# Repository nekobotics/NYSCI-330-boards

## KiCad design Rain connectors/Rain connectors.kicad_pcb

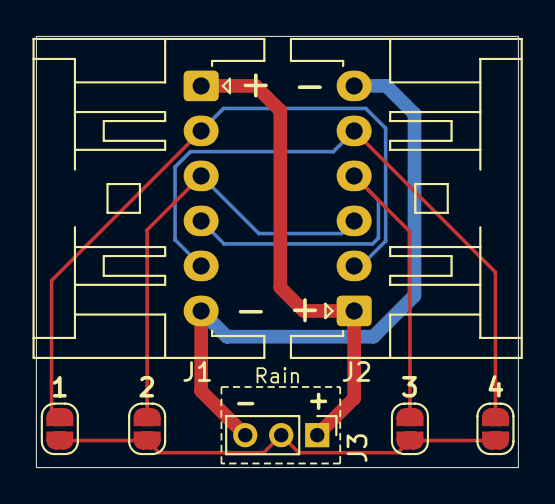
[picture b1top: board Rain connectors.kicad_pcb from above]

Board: 2 copper layers, 26.8 x 24.0 mm, 7 parts (0 on the bottom side), 7 nets.

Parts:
1, 2, 3, 4: Jumper_2_Open; SolderJumper-2_P1.3mm_Open_RoundedPad1.0x1.5mm
J1, J2: Conn_01x06_Socket; JST_XA_S06B-XASK-1_1x06_P2.50mm_Horizontal
J3: Conn_01x03_Socket; PinHeader_1x03_P2.00mm_Vertical

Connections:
+5V: J1.1, J2.1, J3.1
GND: J1.6, J2.6, J3.3
unnamed: 1.2 (B), J1.2, J2.2
unnamed: 2.2 (B), J1.3, J2.3
unnamed: 3.2 (B), J1.4, J2.4
unnamed: 4.2 (B), J1.5, J2.5
unnamed: 1.1 (A), 2.1 (A), 3.1 (A), 4.1 (A), J3.2

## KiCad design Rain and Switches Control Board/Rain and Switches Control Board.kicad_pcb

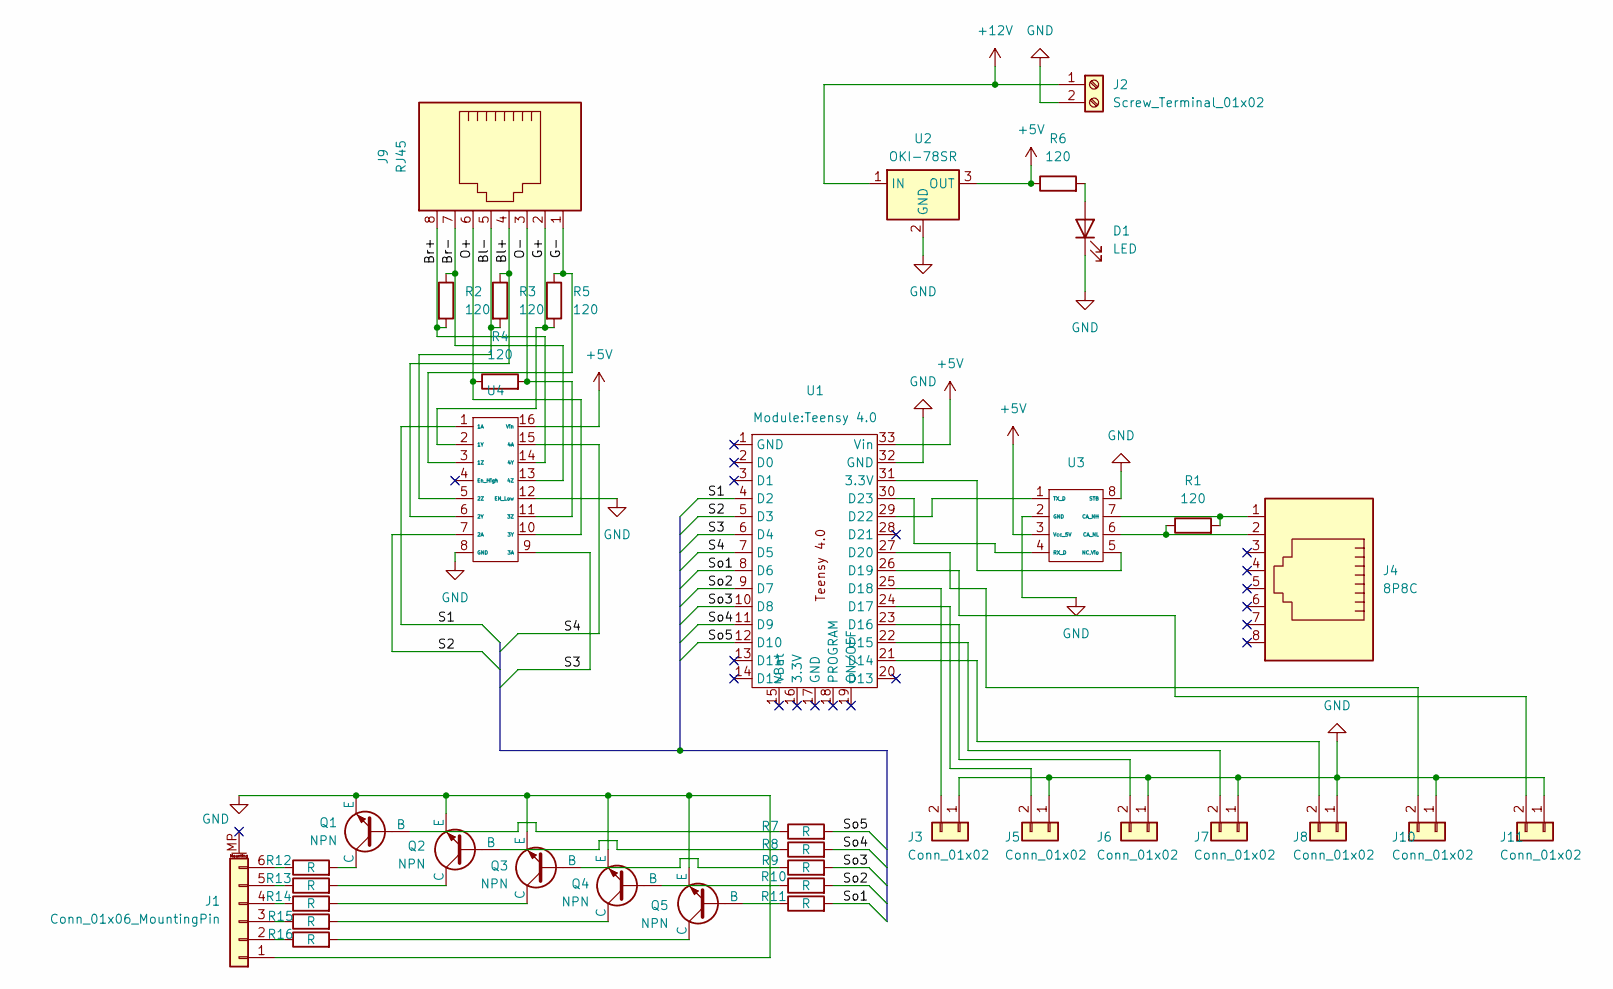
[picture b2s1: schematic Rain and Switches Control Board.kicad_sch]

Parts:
D1: LED; LED_D3.0mm
J1: Conn_01x06_MountingPin; PhoenixContact_MC_1,5_6-G-3.5_1x06_P3.50mm_Horizontal
J2: Screw_Terminal_01x02; TerminalBlock_Wago_2x1_2604_1102
J3, J5, J6, J7, J8, J10, J11: Conn_01x02; TerminalBlock_Altech_AK300-2_P5.00mm
J4: 8P8C; RJ45_Ninigi_GE
J9: RJ45; RJ45_Ninigi_GE; LCSC C708636
Q1, Q2, Q3, Q4, Q5: NPN; TO-92
R1, R2, R3, R4, R5, R6: 120; R_1206_3216Metric
R7, R8, R9, R10, R11: R; R_0805_2012Metric
R12, R13, R14, R15, R16: R; R_1206_3216Metric
U1: Teensy 4.0
U2: OKI-78SR; Converter_DCDC_Murata_OKI-78SR_Vertical
U3: TCAN1462VDRQ1
U4: DS26C31TMX

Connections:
+5V: R6.1, U1.33 (Vin), U2.3 (OUT), U3.3 (Vcc_5V), U4.16 (Vin)
+12V: J2.1, U2.1 (IN)
/Bl+: J9.4, R3.1, U4.6 (2Y)
/Bl-: J9.5, R3.2, U4.5 (2Z)
/Br+: J9.8, R2.2, U4.14 (4Y)
/Br-: J9.7, R2.1, U4.13 (4Z)
/G+: J9.2, R5.2, U4.2 (1Y)
/G-: J9.1, R5.1, U4.3 (1Z)
/O+: J9.6, R4.1, U4.10 (3Y)
/O-: J9.3, R4.2, U4.11 (3Z)
/S1: U1.4 (D2), U4.1 (1A)
/S2: U1.5 (D3), U4.7 (2A)
/S3: U1.6 (D4), U4.9 (3A)
/S4: U1.7 (D5), U4.15 (4A)
/So1: R11.2, U1.8 (D6)
/So2: R10.2, U1.9 (D7)
/So3: R9.2, U1.10 (D8)
/So4: R8.2, U1.11 (D9)
/So5: R7.2, U1.12 (D10)
GND: D1.1 (K), J1.1, J2.2, J3.1, J5.1, J6.1, J7.1, J8.1, J10.1, J11.1, Q1.3 (E), Q2.3 (E), Q3.3 (E), Q4.3 (E), Q5.3 (E), U1.32 (GND), U2.2 (GND), U3.2 (GND), U3.8 (STB), U4.8 (GND), U4.12 (EN_Low)
unnamed: D1.2 (A), R6.2
unnamed: J1.2, R16.1
unnamed: J1.3, R15.1
unnamed: J1.4, R14.1
unnamed: J1.5, R13.1
unnamed: J1.6, R12.1
unnamed: J3.2, U1.25 (D18)
unnamed: J5.2, U1.24 (D17)
unnamed: J6.2, U1.23 (D16)
unnamed: J7.2, U1.22 (D15)
unnamed: J8.2, U1.21 (D14)
unnamed: J10.2, U1.27 (D20)
unnamed: J11.2, U1.26 (D19)
unnamed: Q1.2 (B), R7.1
unnamed: Q1.1 (C), R12.2
unnamed: Q2.2 (B), R8.1
unnamed: Q2.1 (C), R13.2
unnamed: Q3.2 (B), R9.1
unnamed: Q3.1 (C), R14.2
unnamed: Q4.2 (B), R10.1
unnamed: Q4.1 (C), R15.2
unnamed: Q5.2 (B), R11.1
unnamed: Q5.1 (C), R16.2
unnamed: U1.29 (D22), U3.1 (TX_D)
unnamed: U1.30 (D23), U3.4 (RX_D)
unnamed: J4.1, R1.2, U3.7 (CA_NH)
unnamed: J4.2, R1.1, U3.6 (CA_NL)
unnamed: U1.31 (3.3V), U3.5 (NC,Vio)

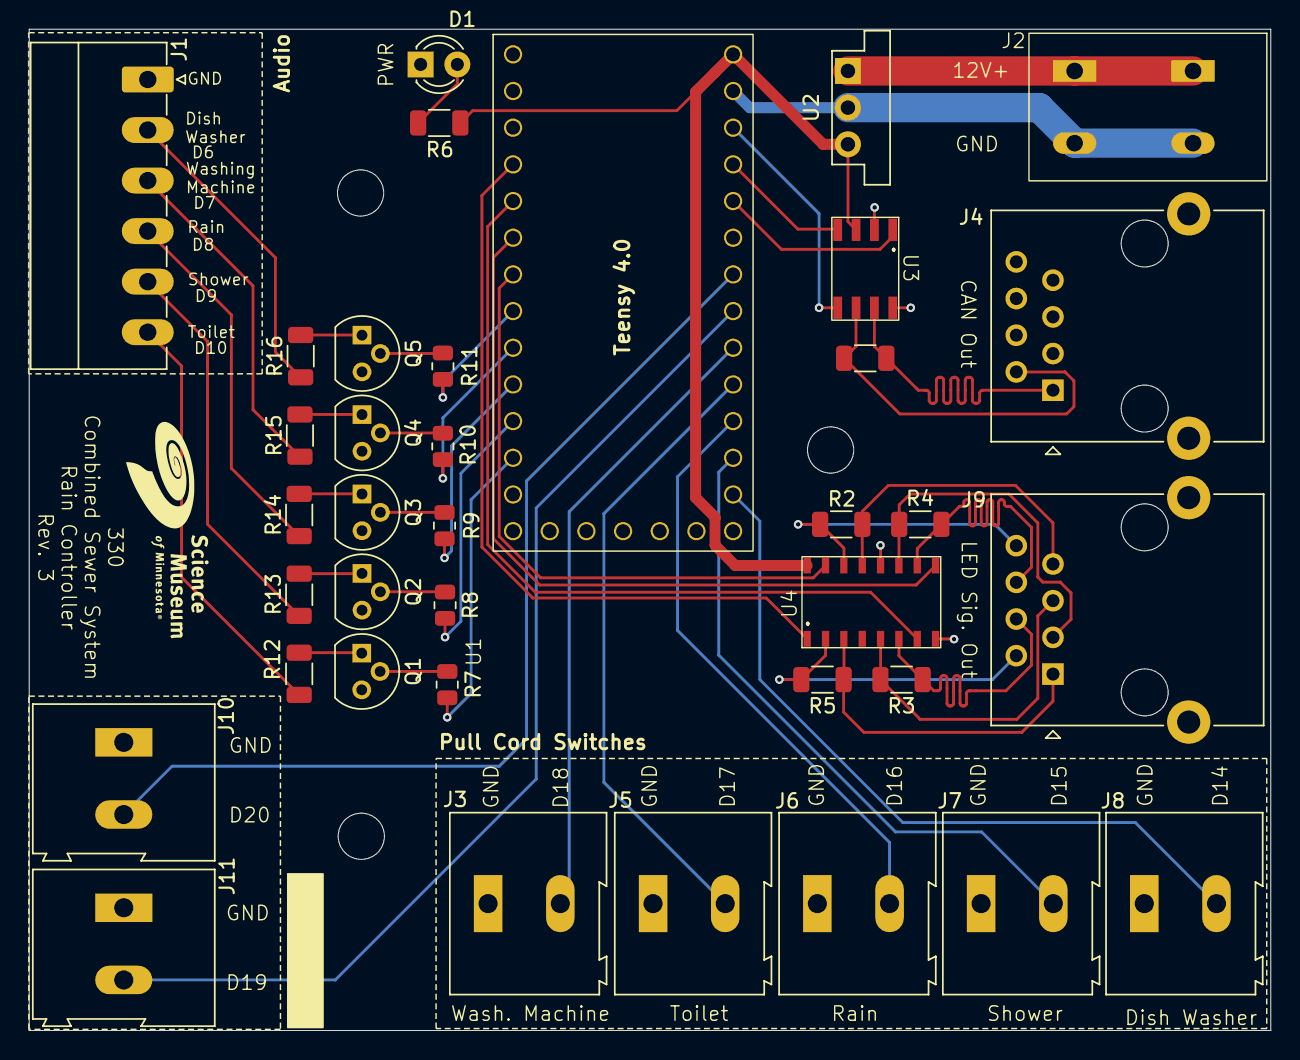
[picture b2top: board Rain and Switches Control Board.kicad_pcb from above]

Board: 2 copper layers, 86.0 x 69.3 mm, 37 parts (0 on the bottom side), 48 nets.

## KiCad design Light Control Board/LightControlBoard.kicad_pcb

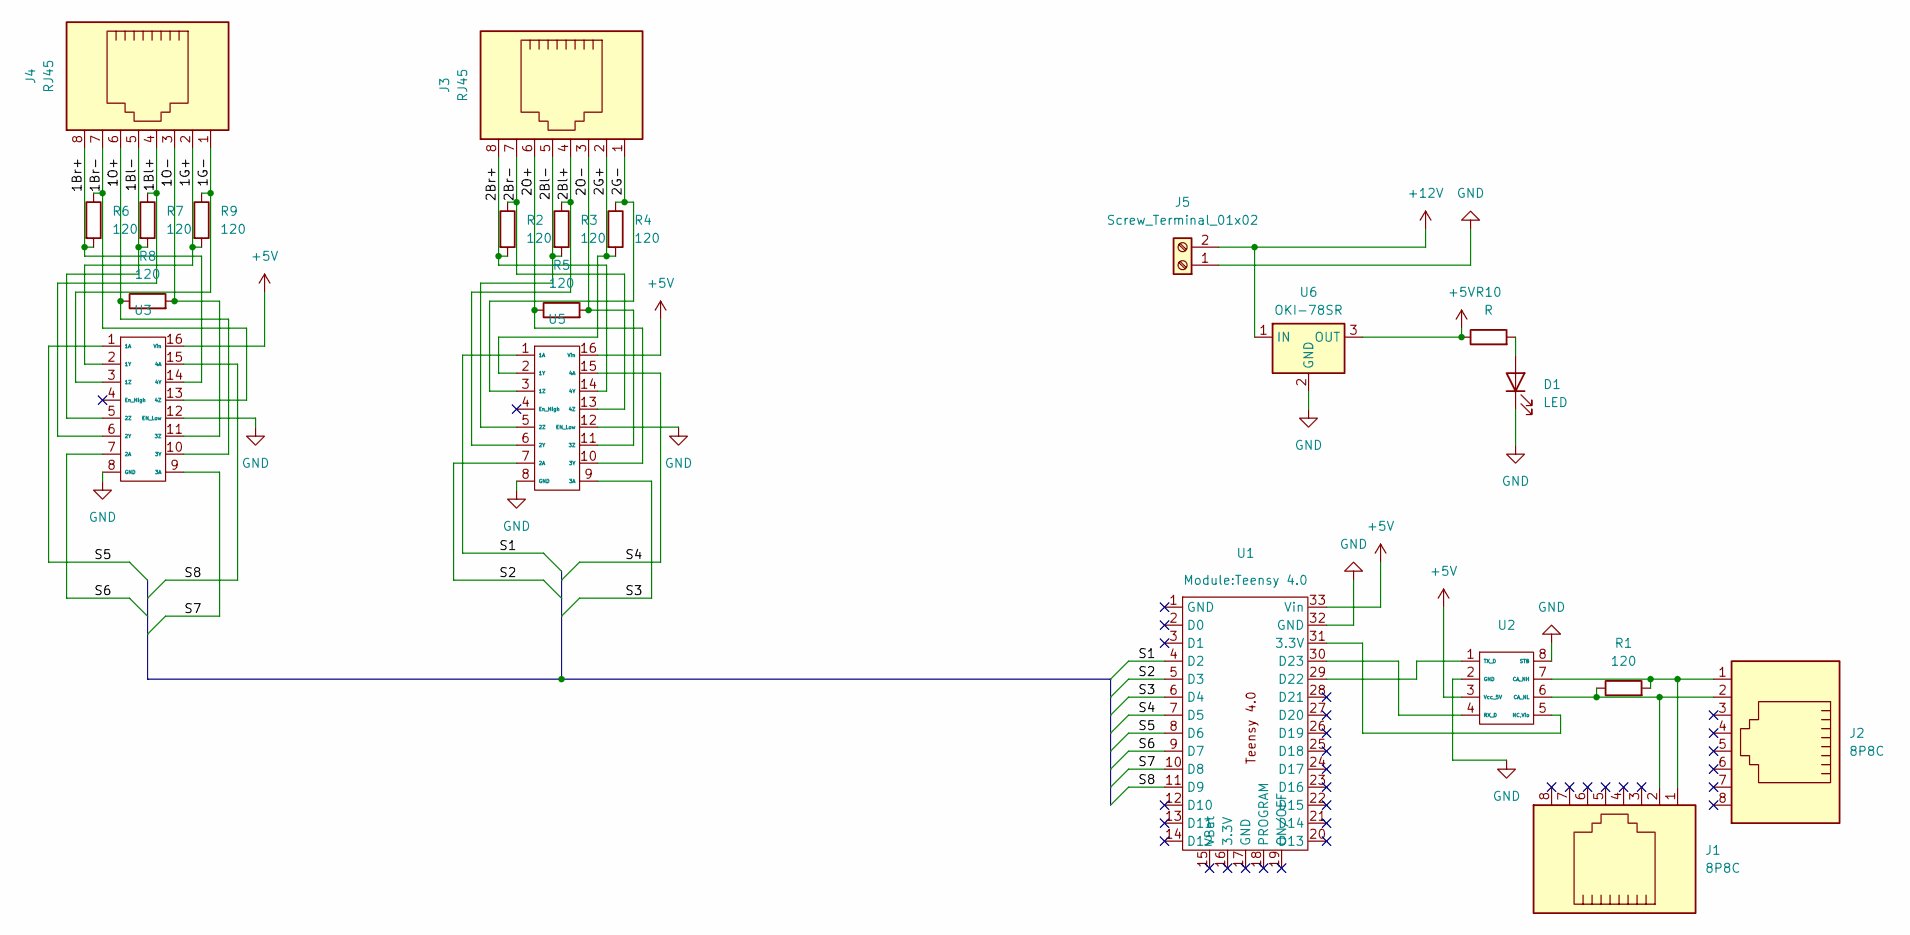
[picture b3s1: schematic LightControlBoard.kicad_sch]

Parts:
D1: LED; LED_D3.0mm
J1, J2: 8P8C; RJ45_Ninigi_GE
J3, J4: RJ45; RJ45_Ninigi_GE; LCSC C708636
J5: Screw_Terminal_01x02; TerminalBlock_Wago_2x1_2604_1102
R1: 120; R_LDR_5.0x4.1mm_P3mm_Vertical
R2, R3, R4, R5, R6, R7, R8, R9: 120; R_1206_3216Metric
R10: R; R_1206_3216Metric
U1: Teensy 4.0
U2: TCAN1462VDRQ1
U3, U5: DS26C31TMX
U6: OKI-78SR; Converter_DCDC_Murata_OKI-78SR_Vertical

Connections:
+5V: R10.1, U1.33 (Vin), U2.3 (Vcc_5V), U3.16 (Vin), U5.16 (Vin), U6.3 (OUT)
+12V: J5.2, U6.1 (IN)
/1Bl+: J4.4, R7.1, U3.6 (2Y)
/1Bl-: J4.5, R7.2, U3.5 (2Z)
/1Br+: J4.8, R6.2, U3.14 (4Y)
/1Br-: J4.7, R6.1, U3.13 (4Z)
/1G+: J4.2, R9.2, U3.2 (1Y)
/1G-: J4.1, R9.1, U3.3 (1Z)
/1O+: J4.6, R8.1, U3.10 (3Y)
/1O-: J4.3, R8.2, U3.11 (3Z)
/2Bl+: J3.4, R3.1, U5.6 (2Y)
/2Bl-: J3.5, R3.2, U5.5 (2Z)
/2Br+: J3.8, R2.2, U5.14 (4Y)
/2Br-: J3.7, R2.1, U5.13 (4Z)
/2G+: J3.2, R4.2, U5.2 (1Y)
/2G-: J3.1, R4.1, U5.3 (1Z)
/2O+: J3.6, R5.1, U5.10 (3Y)
/2O-: J3.3, R5.2, U5.11 (3Z)
/S1: U1.4 (D2), U5.1 (1A)
/S2: U1.5 (D3), U5.7 (2A)
/S3: U1.6 (D4), U5.9 (3A)
/S4: U1.7 (D5), U5.15 (4A)
/S5: U1.8 (D6), U3.1 (1A)
/S6: U1.9 (D7), U3.7 (2A)
/S7: U1.10 (D8), U3.9 (3A)
/S8: U1.11 (D9), U3.15 (4A)
GND: D1.1 (K), J5.1, U1.32 (GND), U2.2 (GND), U2.8 (STB), U3.8 (GND), U3.12 (EN_Low), U5.8 (GND), U5.12 (EN_Low), U6.2 (GND)
unnamed: D1.2 (A), R10.2
unnamed: U1.29 (D22), U2.1 (TX_D)
unnamed: U1.30 (D23), U2.4 (RX_D)
unnamed: J1.1, J2.1, R1.2, U2.7 (CA_NH)
unnamed: J1.2, J2.2, R1.1, U2.6 (CA_NL)
unnamed: U1.31 (3.3V), U2.5 (NC,Vio)

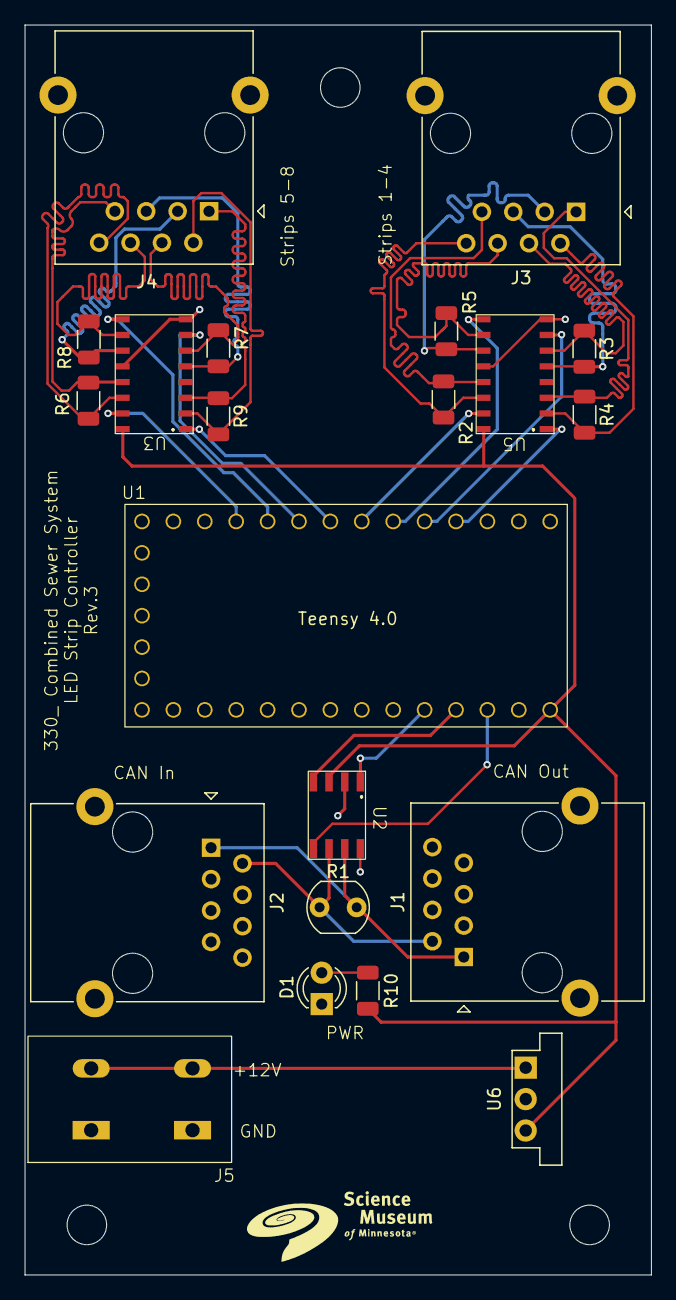
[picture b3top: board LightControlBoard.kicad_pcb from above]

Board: 2 copper layers, 50.7 x 101.1 mm, 21 parts (0 on the bottom side), 33 nets.

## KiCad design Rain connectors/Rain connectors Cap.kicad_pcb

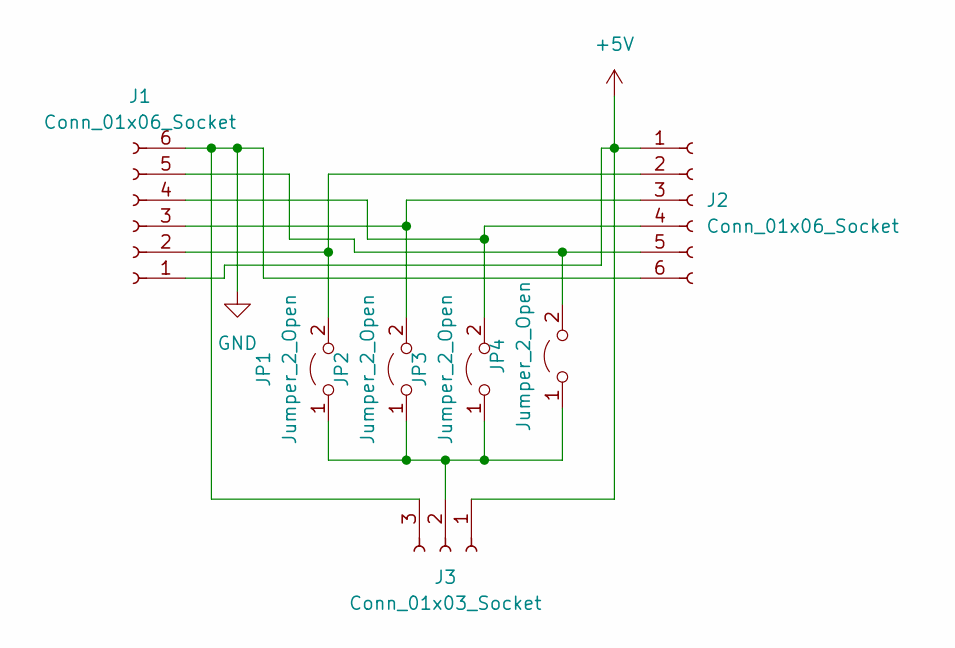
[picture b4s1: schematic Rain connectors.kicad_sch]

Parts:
J1, J2: Conn_01x06_Socket; JST_XA_S06B-XASK-1_1x06_P2.50mm_Horizontal
J3: Conn_01x03_Socket; PinHeader_1x03_P2.00mm_Vertical
JP1, JP2, JP3, JP4: Jumper_2_Open; SolderJumper-2_P1.3mm_Open_RoundedPad1.0x1.5mm

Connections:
+5V: J1.1, J2.1, J3.1; also elsewhere on the board
GND: J1.6, J2.6, J3.3; also elsewhere on the board
unnamed: J1.2, J2.2, JP1.2 (B)
unnamed: J1.3, J2.3, JP2.2 (B)
unnamed: J1.4, J2.4, JP3.2 (B)
unnamed: J1.5, J2.5, JP4.2 (B)
unnamed: J3.2, JP1.1 (A), JP2.1 (A), JP3.1 (A), JP4.1 (A)

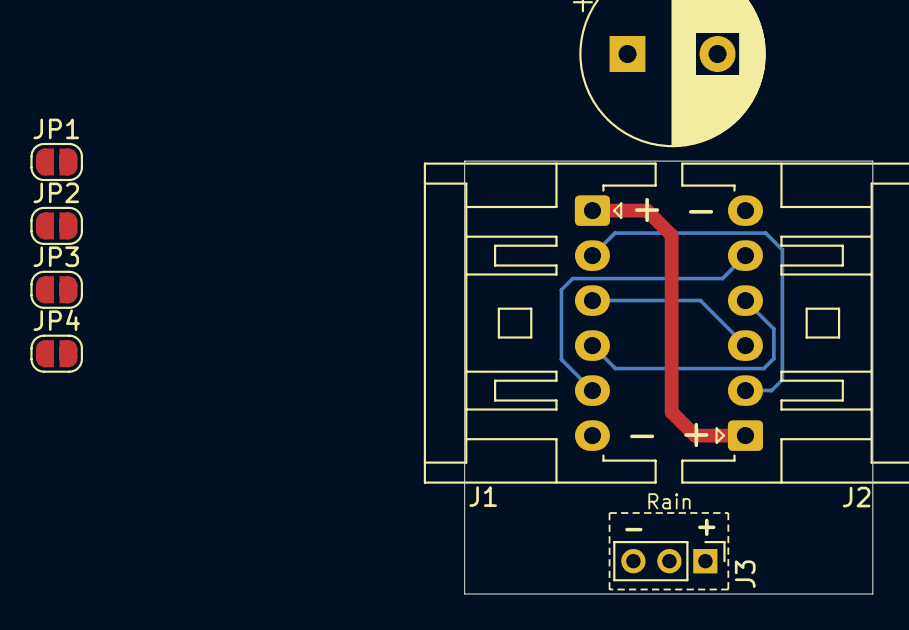
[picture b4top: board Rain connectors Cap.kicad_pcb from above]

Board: 2 copper layers, 22.7 x 24.0 mm, 8 parts (0 on the bottom side), 7 nets.

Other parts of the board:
C1: C_Polarized; CP_Radial_D10.0mm_P5.00mm

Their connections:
+5V: C1.1; also elsewhere on the board
GND: C1.2; also elsewhere on the board

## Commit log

2024-12-10 check on rev.2 of Control boards and rev.3 of led segments
2024-12-12 Check to see if the rain connectors v.2. needs updating
2024-12-12 check board revisions
2025-01-29 Rev. 3
